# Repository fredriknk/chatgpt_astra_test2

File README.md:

# Codex EE-design test, human foreword
So, background, i saw the Chatgpt Astra demo for kicad design and wanted to try it out myself, i just have an Open AI plus subscription, so i had to use the LOW setting to not nuke my usage immidiatly. But it managed to make this design within my three usage resets. Im pretty damn impressed with the result, its not perfect, but it is a fully routed design with no drc errors made in under 3 hours with a 20$ subscription. I would say the most lacking part is the schematic, it is not very human readable, but i do understand why it is made as it is as ive tried multiple MCP's for ee design and wires in schematics becomes a hot mess with more than a few components. But now im out of resets so i thought i stop here. 

Initial repo: [my kicad template](https://github.com/fredriknk/kicad_template)
Initial promt: [prompt](https://github.com/fredriknk/chatgpt_astra_test2/blob/main/Prompt.md)

After the initial prompt i basically just said "Sounds like a good idea" to any questions

# ESP32 24 V current-loop interface - Rev A

A 100 x 80 mm, four-layer prototype with an ESP32-S3, one protected 4-20 mA input, and one sourcing 4-20 mA output. Power and signal grounds are shared; this is not an isolated interface.

The layout is fully routed. Final KiCad 9 checks report **zero ERC violations, zero DRC violations, zero unconnected items, and zero schematic/PCB parity errors**. The independent connectivity check covers 93 components and 273 connected pins. Hardware accuracy, fault survival, thermal performance, EMC and USB interoperability still require prototype testing.

| Start here | Contents |
|---|---|
| [Design and bring-up guide](DOCUMENTATION/DESIGN.md) | Wiring, protection, firmware interface, calibration and bench tests |
| [Fabrication notes](DOCUMENTATION/FABRICATION.md) | Stackup, USB impedance, assembly and procurement |
| [KiCad project](CAD/chatgpt_astra_test2/chatgpt_astra_test2.kicad_pro) | Editable schematic and PCB, with local libraries |
| [Schematic PDF](DOCUMENTATION/chatgpt_astra_test2_schematic.pdf) | Five schematic sheets |
| [Board layers PDF](DOCUMENTATION/chatgpt_astra_test2_board_prints.pdf) | Copper, mask, silkscreen and assembly views |
| [Layout verification](DOCUMENTATION/board_review/README.md) | Checks, USB length audit and milestones |
| [Manufacturing outputs](PRODUCTION/20260907_1303_chatgpt_astra_test2/) | Four copper layers, masks, silk, paste, outline, drills, BOM and placement CSV |
| [CI build log](DOCUMENTATION/ci_build.log) | Successful complete output-pipeline run |

## Regenerate and check

On Windows with KiCad 9 installed, run `generate_outputs.bat`. The equivalent command is:

```text
python build_outputs.py --project CAD/chatgpt_astra_test2/chatgpt_astra_test2.kicad_pro --iso --zip
```

The script fails on ERC/DRC violations and generates a new timestamped production folder. It does not place an order. `generate_outputs.sh` provides the same entry point on systems with KiCad on PATH. Set `KICAD9_3DMODEL_DIR` to the installed KiCad model library if needed.

The BOM is an engineering BOM: semiconductor part numbers are in Value fields, while several passives retain value/rating specifications rather than purchasing MPNs. Review procurement before ordering. Three installed 3D models are missing (USB connector, DAC and current driver); their footprints are present, but the STEP/render is not a complete mechanical assembly model.

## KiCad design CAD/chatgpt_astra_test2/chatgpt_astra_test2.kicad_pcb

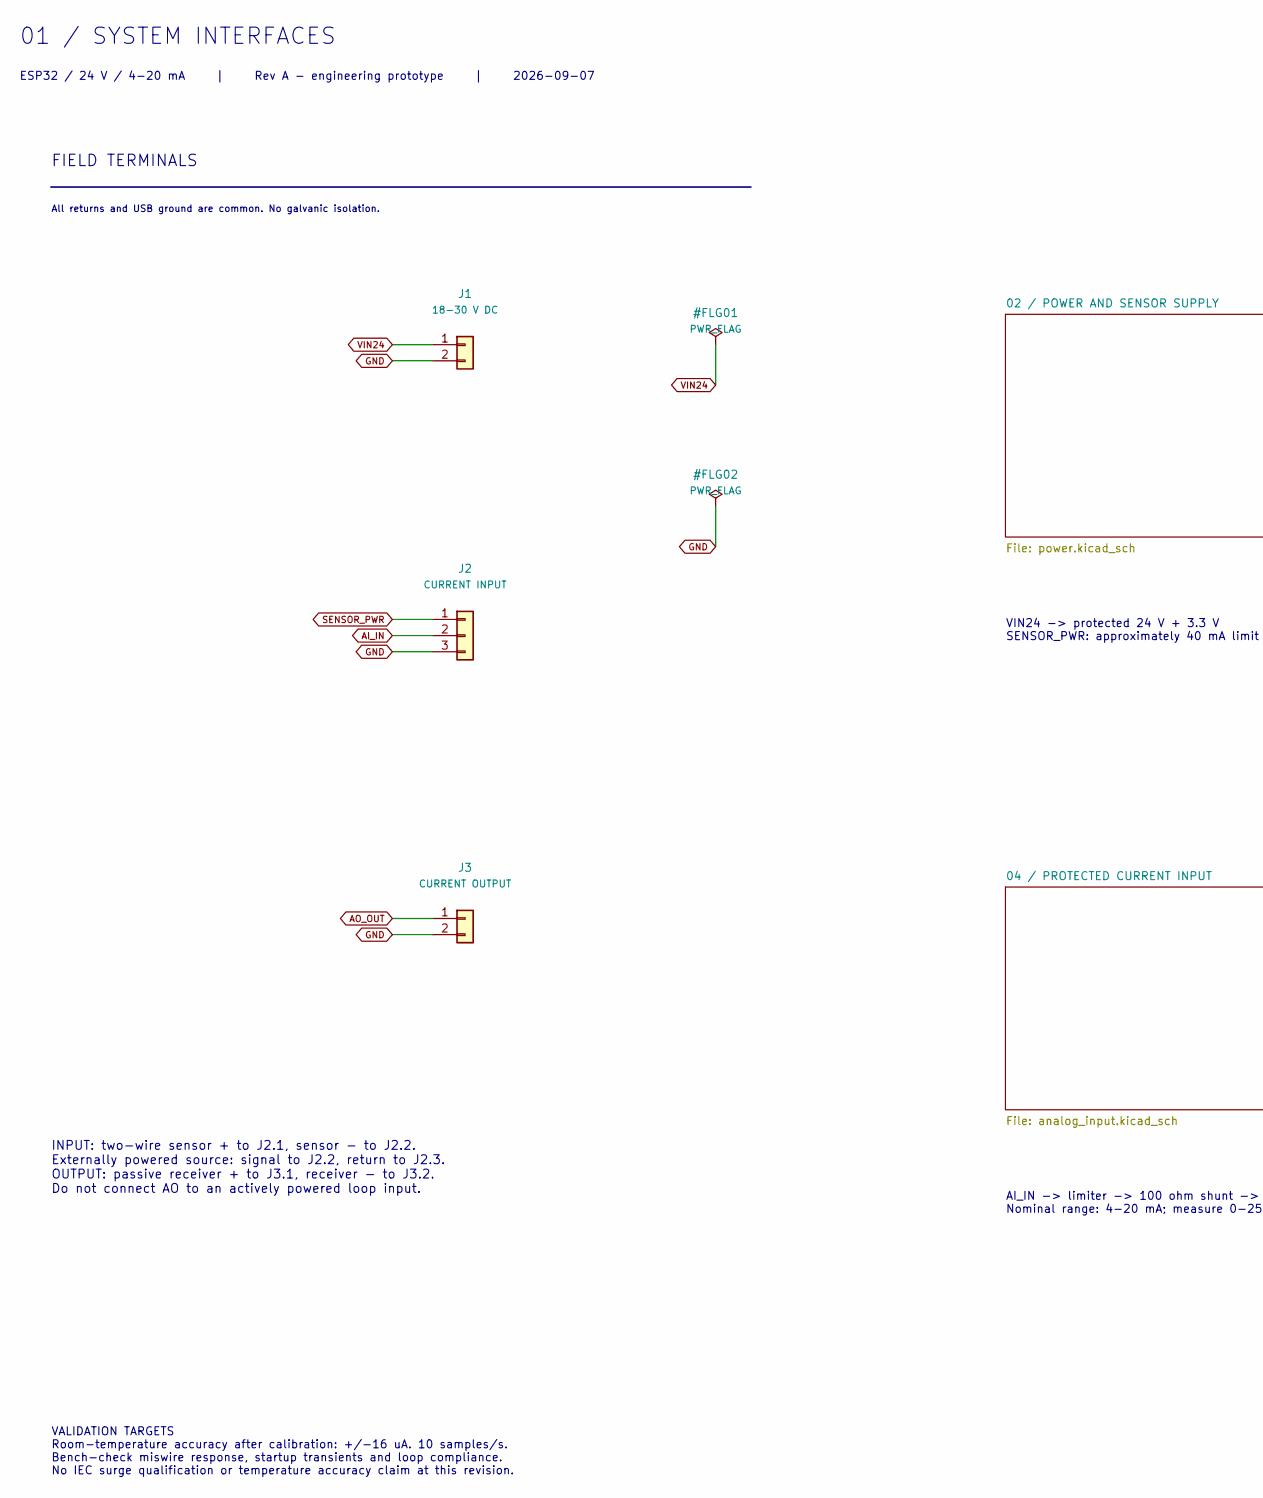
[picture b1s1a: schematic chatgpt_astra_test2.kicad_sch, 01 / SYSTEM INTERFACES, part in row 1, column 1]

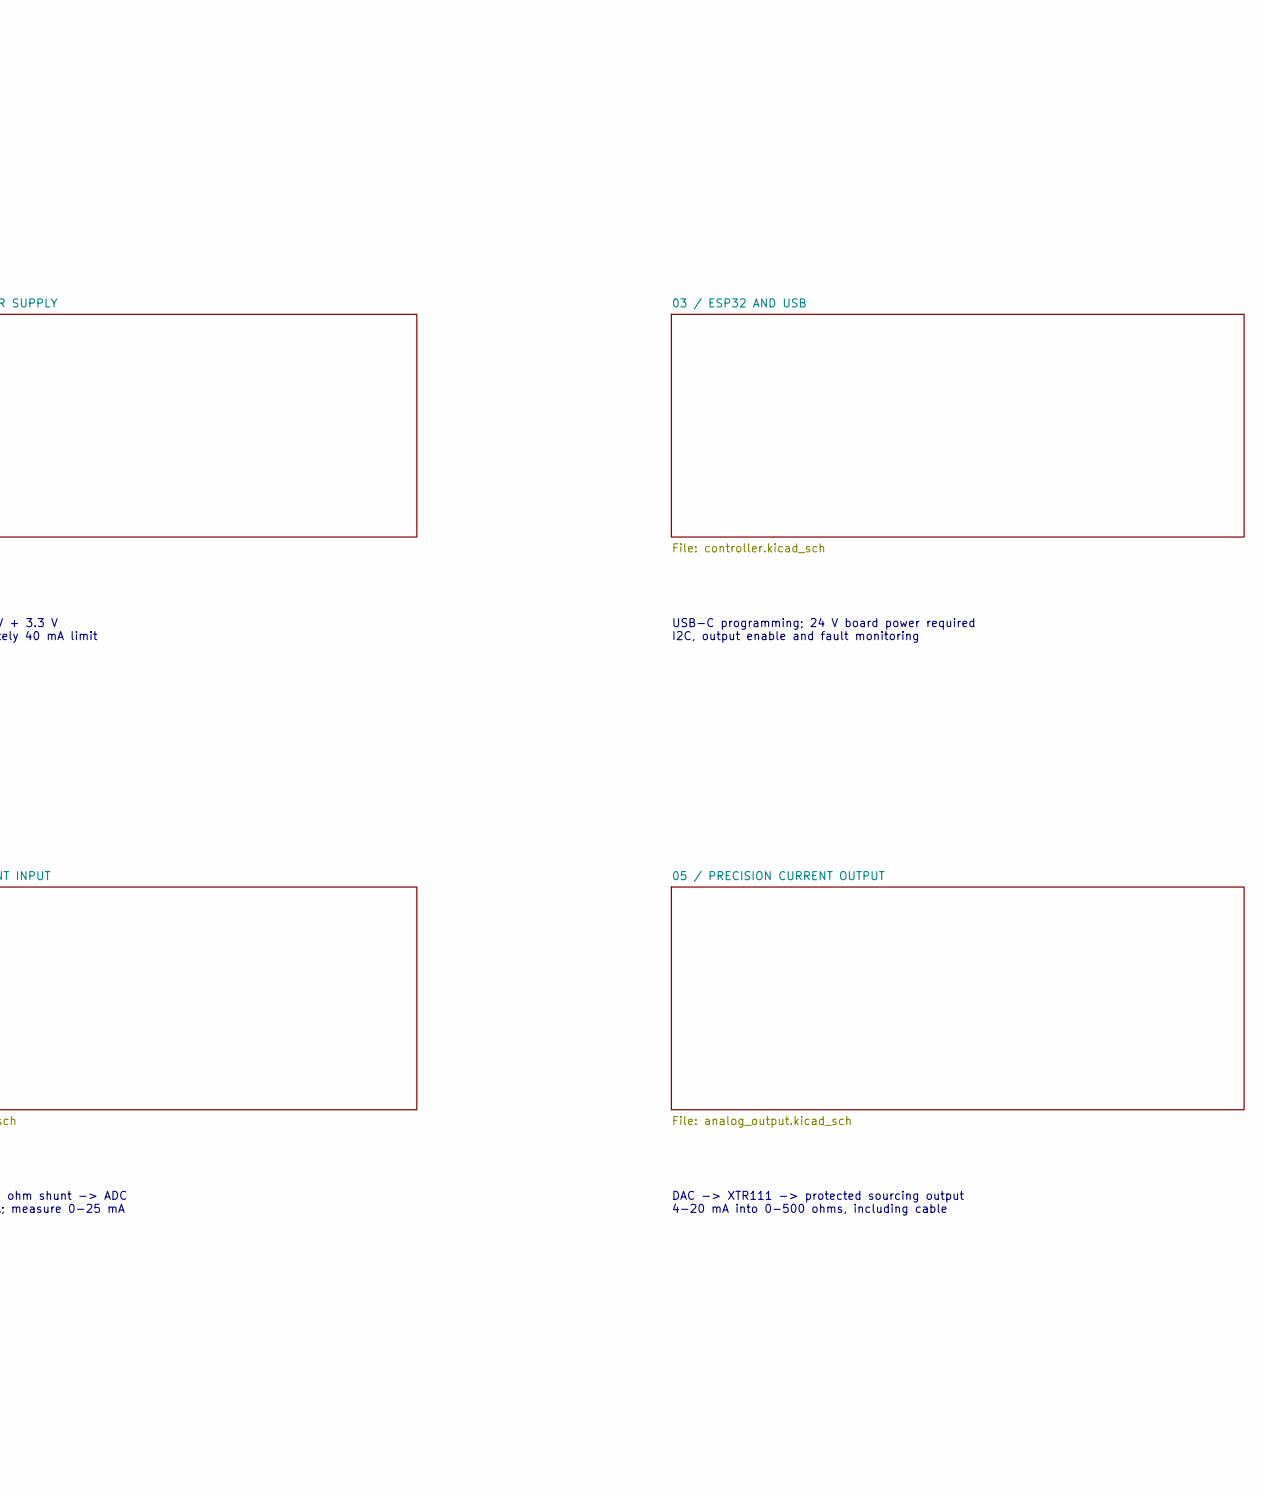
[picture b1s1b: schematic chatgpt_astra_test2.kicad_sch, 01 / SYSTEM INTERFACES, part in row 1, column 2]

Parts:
J1: 18-30 V DC; TerminalBlock_Phoenix_MKDS-1,5-2-5.08_1x02_P5.08mm_Horizont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
J2: CURRENT INPUT; TerminalBlock_Phoenix_MKDS-1,5-3-5.08_1x03_P5.08mm_Horizont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
J3: CURRENT OUTPUT; TerminalBlock_Phoenix_MKDS-1,5-2-5.08_1x02_P5.08mm_Horizont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

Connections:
AI_IN: J2.2; also elsewhere on the board
AO_OUT: J3.1; also elsewhere on the board
GND: J1.2, J2.3, J3.2; also elsewhere on the board
SENSOR_PWR: J2.1; also elsewhere on the board
VIN24: J1.1; also elsewhere on the board

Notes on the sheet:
01 / SYSTEM INTERFACES
ESP32 / 24 V / 4-20 mA | Rev A - engineering prototype | 2026-09-07
FIELD TERMINALS
All returns and USB ground are common. No galvanic isolation.
INPUT: two-wire sensor + to J2.1, sensor - to J2.2. Externally powered source: signal to J2.2, return to J2.3. OUTPUT: passive receiver + to J3.1, receiver - to J3.2. Do not connect AO to an actively powered loop input.
VIN24 -> protected 24 V + 3.3 V SENSOR_PWR: approximately 40 mA limit
USB-C programming; 24 V board power required I2C, output enable and fault monitoring
AI_IN -> limiter -> 100 ohm shunt -> ADC Nominal range: 4-20 mA; measure 0-25 mA
DAC -> XTR111 -> protected sourcing output 4-20 mA into 0-500 ohms, including cable
VALIDATION TARGETS Room-temperature accuracy after calibration: +/-16 uA. 10 samples/s. Bench-check miswire response, startup transients and loop compliance. No IEC surge qualification or temperature accuracy claim at this revision.

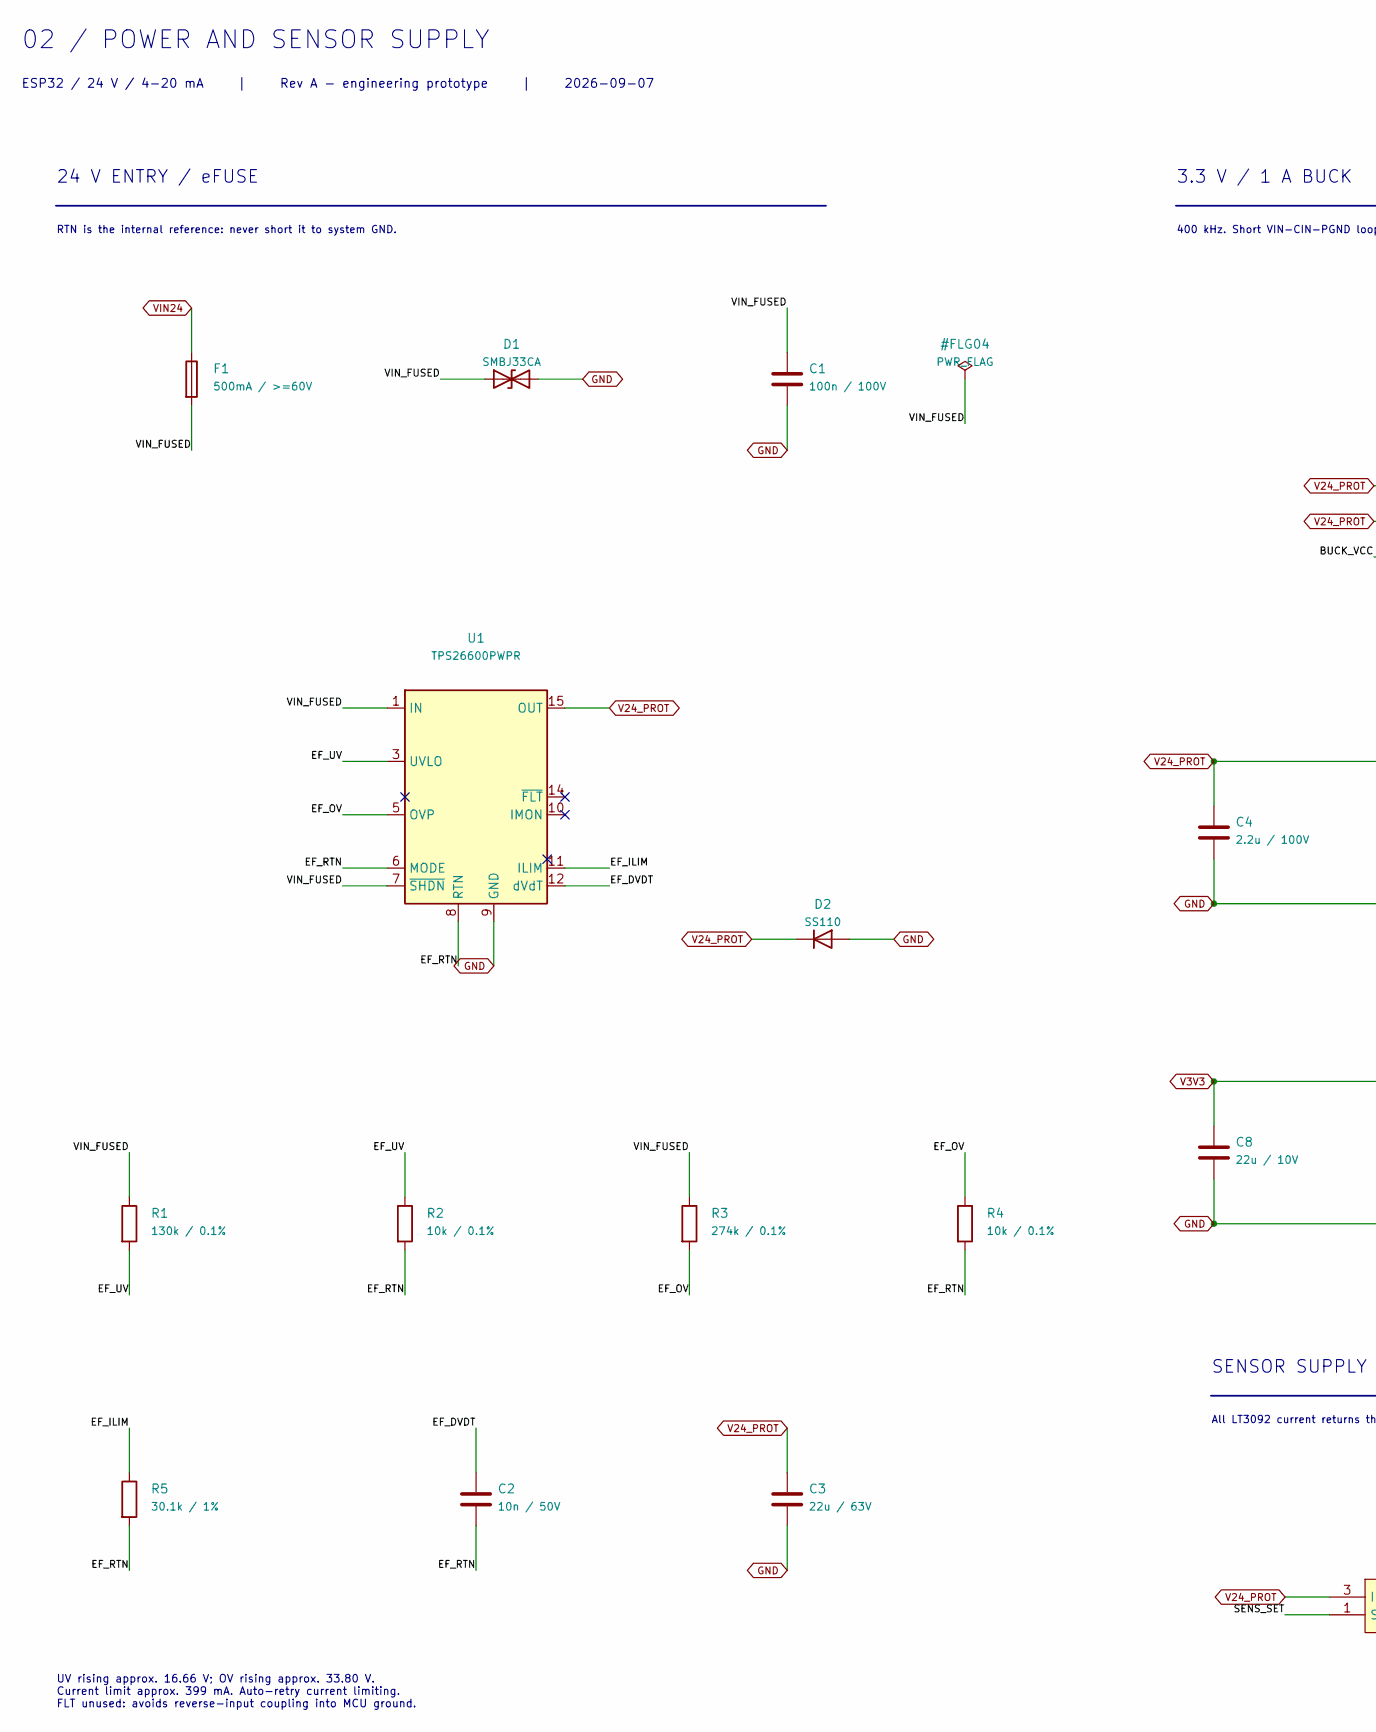
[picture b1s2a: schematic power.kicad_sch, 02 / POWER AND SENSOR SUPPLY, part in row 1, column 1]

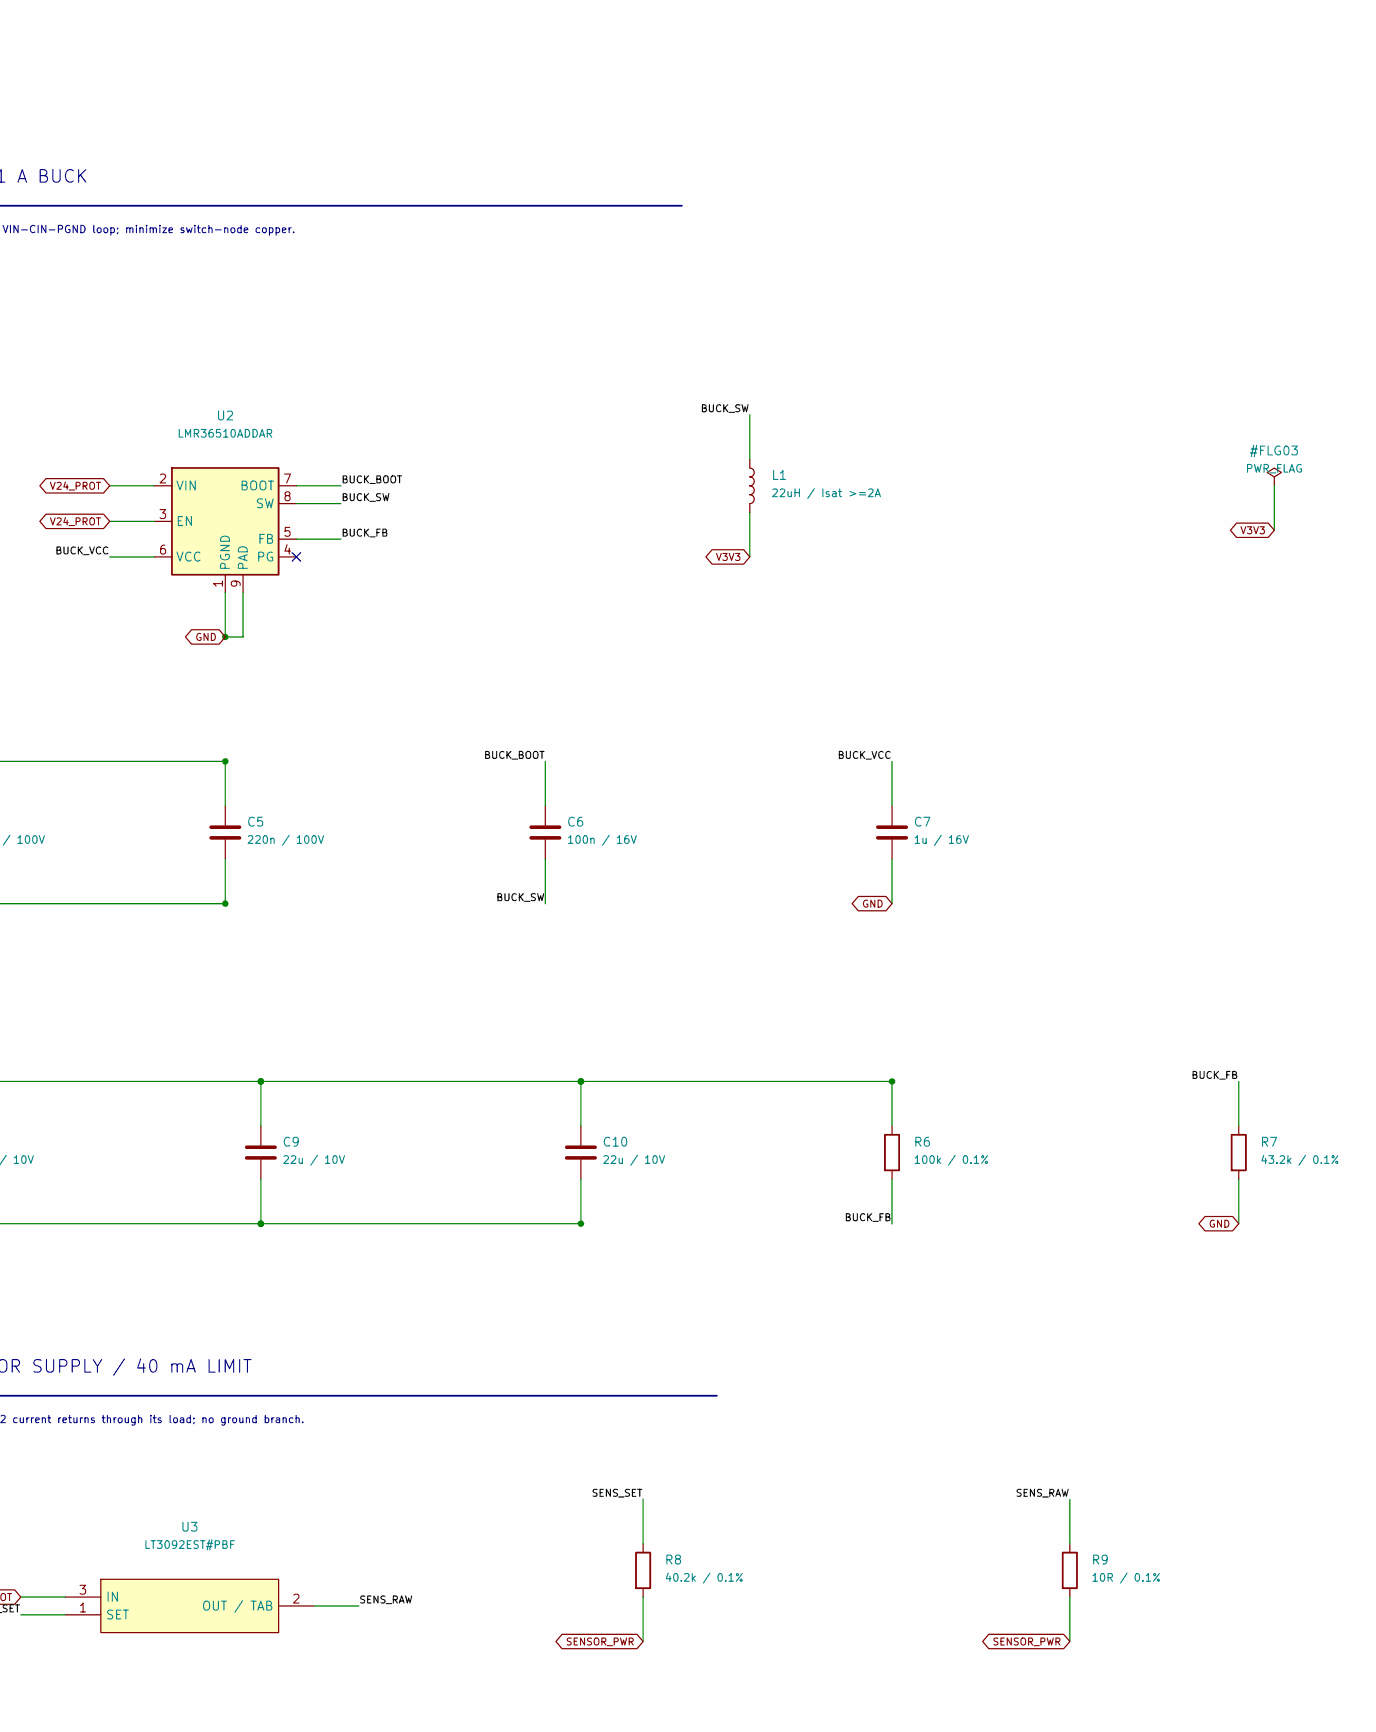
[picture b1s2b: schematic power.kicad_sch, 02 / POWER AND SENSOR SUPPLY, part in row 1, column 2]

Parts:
C1: 100n / 100V; C_0805_2012Metric
C2: 10n / 50V; C_0805_2012Metric
C3: 22u / 63V; C_1210_3225Metric
C4: 2.2u / 100V; C_1210_3225Metric
C5: 220n / 100V; C_0805_2012Metric
C6: 100n / 16V; C_0805_2012Metric
C7: 1u / 16V; C_0805_2012Metric
C8, C9, C10: 22u / 10V; C_1206_3216Metric
D1: SMBJ33CA; D_SMB
D2: SS110; D_SMA
F1: 500mA / >=60V; Fuse_1206_3216Metric
L1: 22uH / Isat >=2A; L_Bourns_SRN6045TA
R1: 130k / 0.1%; R_0805_2012Metric
R2, R4: 10k / 0.1%; R_0805_2012Metric
R3: 274k / 0.1%; R_0805_2012Metric
R5: 30.1k / 1%; R_0805_2012Metric
R6: 100k / 0.1%; R_0805_2012Metric
R7: 43.2k / 0.1%; R_0805_2012Metric
R8: 40.2k / 0.1%; R_0805_2012Metric
R9: 10R / 0.1%; R_0805_2012Metric
U1: TPS26600PWPR; HTSSOP-16-1EP_4.4x5mm_P0.65mm_EP3.4x5mm_Mask2.66x2.46mm_The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
U2: LMR36510ADDAR; Texas_HTSOP-8-1EP_3.9x4.9mm_P1.27mm_EP2.95x4.9mm_Mask2.4x3.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
U3: LT3092EST#PBF; SOT-223-3_TabPin2

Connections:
/02 / POWER AND SENSOR SUPPLY/BUCK_BOOT: C6.1, U2.7 (BOOT)
/02 / POWER AND SENSOR SUPPLY/BUCK_FB: R6.2, R7.1, U2.5 (FB)
/02 / POWER AND SENSOR SUPPLY/BUCK_SW: C6.2, L1.1, U2.8 (SW)
/02 / POWER AND SENSOR SUPPLY/BUCK_VCC: C7.1, U2.6 (VCC)
/02 / POWER AND SENSOR SUPPLY/EF_DVDT: C2.1, U1.12 (dVdT)
/02 / POWER AND SENSOR SUPPLY/EF_ILIM: R5.1, U1.11 (ILIM)
/02 / POWER AND SENSOR SUPPLY/EF_OV: R3.2, R4.1, U1.5 (OVP)
/02 / POWER AND SENSOR SUPPLY/EF_RTN: C2.2, R2.2, R4.2, R5.2, U1.6 (MODE), U1.8 (RTN), U1.17 (RTN)
/02 / POWER AND SENSOR SUPPLY/EF_UV: R1.2, R2.1, U1.3 (UVLO)
/02 / POWER AND SENSOR SUPPLY/SENS_RAW: R9.1, U3.2 (OUT / TAB)
/02 / POWER AND SENSOR SUPPLY/SENS_SET: R8.1, U3.1 (SET)
/02 / POWER AND SENSOR SUPPLY/VIN_FUSED: C1.1, D1.1 (A1), F1.2, R1.1, R3.1, U1.1 (IN), U1.2 (IN), U1.7 (~SHDN)
GND: C1.2, C3.2, C4.2, C5.2, C7.2, C8.2, C9.2, C10.2, D1.2 (A2), D2.2 (A), R7.2, U1.9 (GND), U2.1 (PGND), U2.9 (PAD); also elsewhere on the board
SENSOR_PWR: R8.2, R9.2; also elsewhere on the board
V3V3: C8.1, C9.1, C10.1, L1.2, R6.1; also elsewhere on the board
V24_PROT: C3.1, C4.1, C5.1, D2.1 (K), U1.15 (OUT), U1.16 (OUT), U2.2 (VIN), U2.3 (EN), U3.3 (IN); also elsewhere on the board
VIN24: F1.1; also elsewhere on the board

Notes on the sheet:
02 / POWER AND SENSOR SUPPLY
ESP32 / 24 V / 4-20 mA | Rev A - engineering prototype | 2026-09-07
24 V ENTRY / eFUSE
RTN is the internal reference: never short it to system GND.
UV rising approx. 16.66 V; OV rising approx. 33.80 V. Current limit approx. 399 mA. Auto-retry current limiting. FLT unused: avoids reverse-input coupling into MCU ground.
3.3 V / 1 A BUCK
400 kHz. Short VIN-CIN-PGND loop; minimize switch-node copper.
SENSOR SUPPLY / 40 mA LIMIT
All LT3092 current returns through its load; no ground branch.

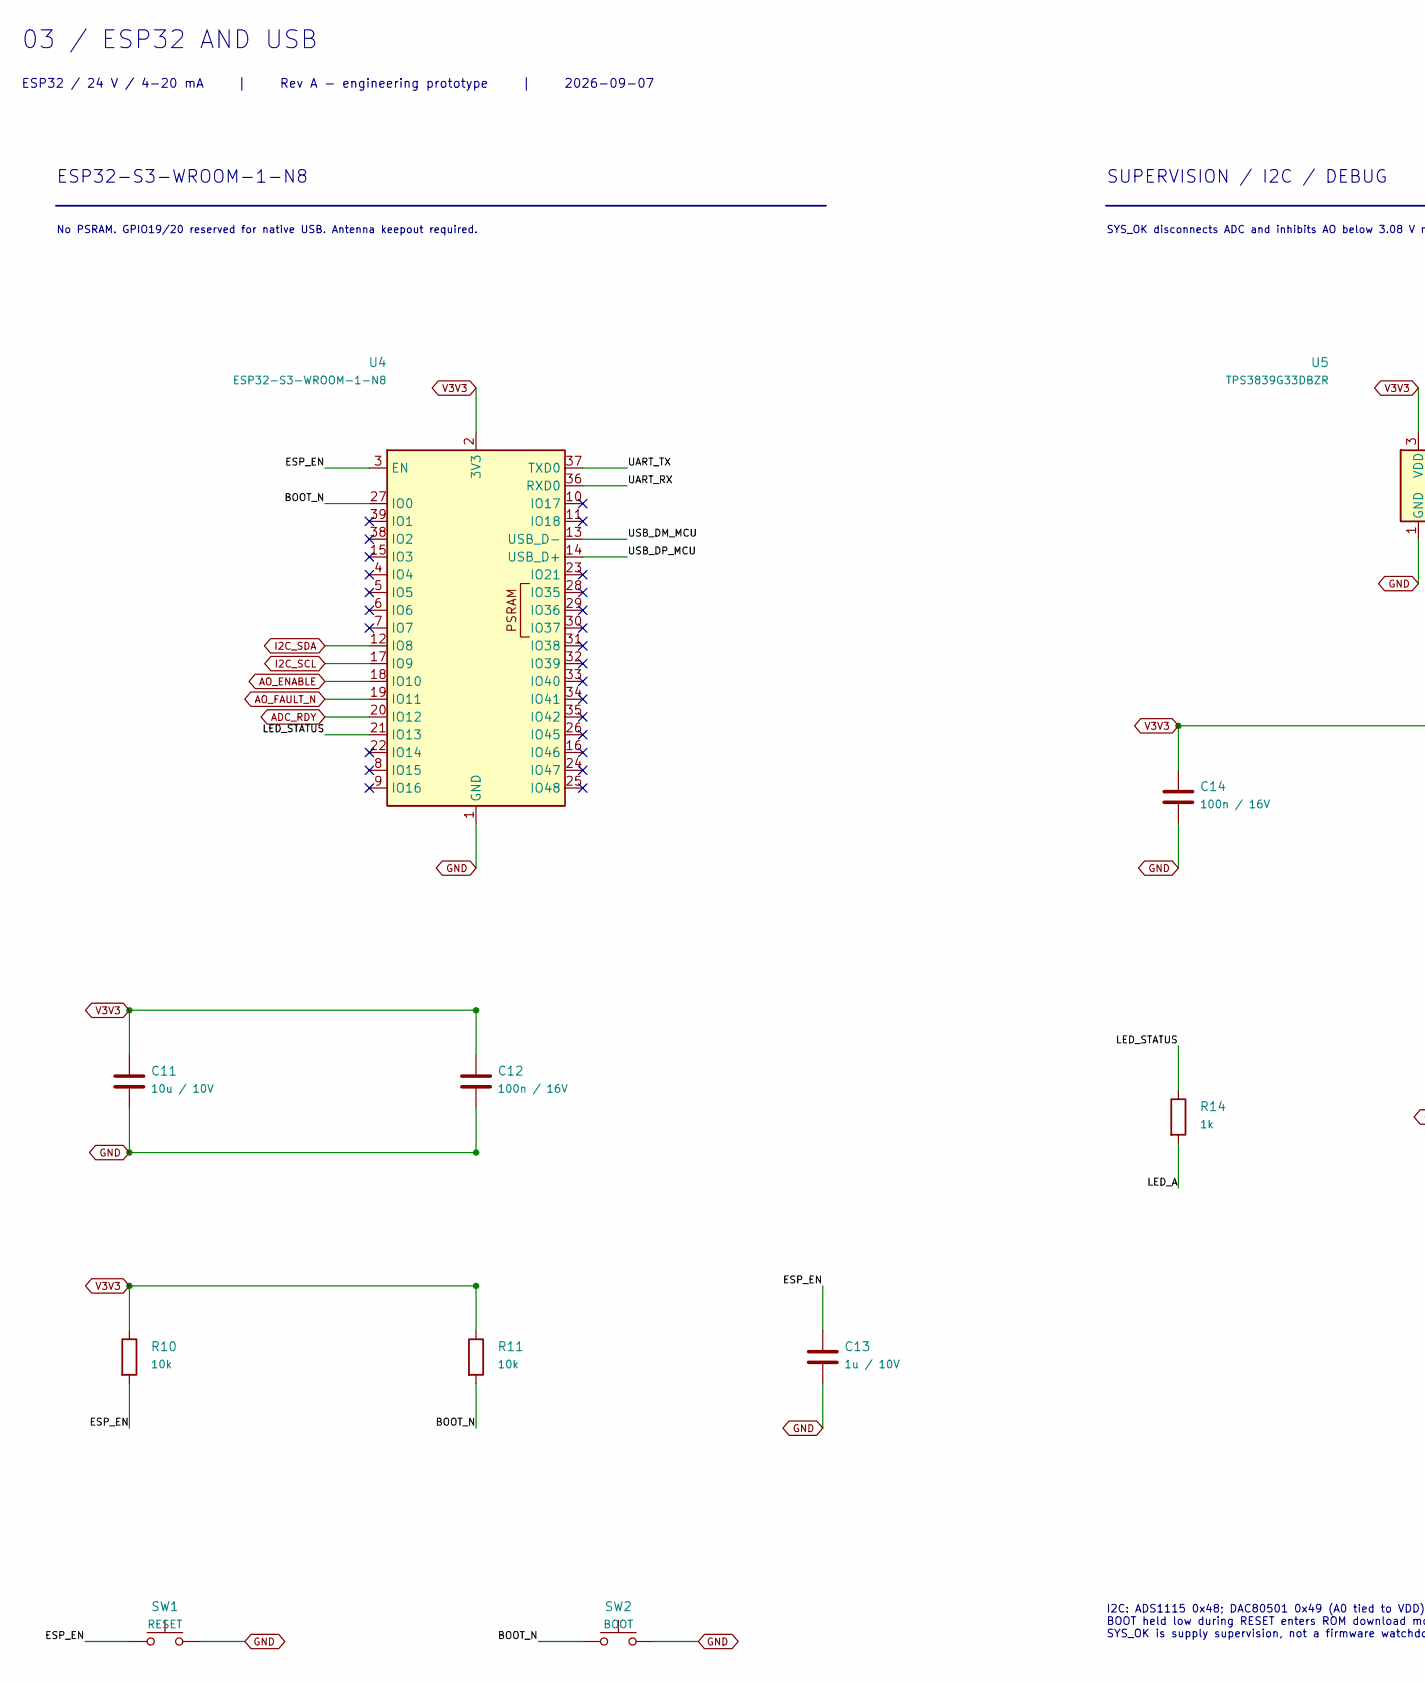
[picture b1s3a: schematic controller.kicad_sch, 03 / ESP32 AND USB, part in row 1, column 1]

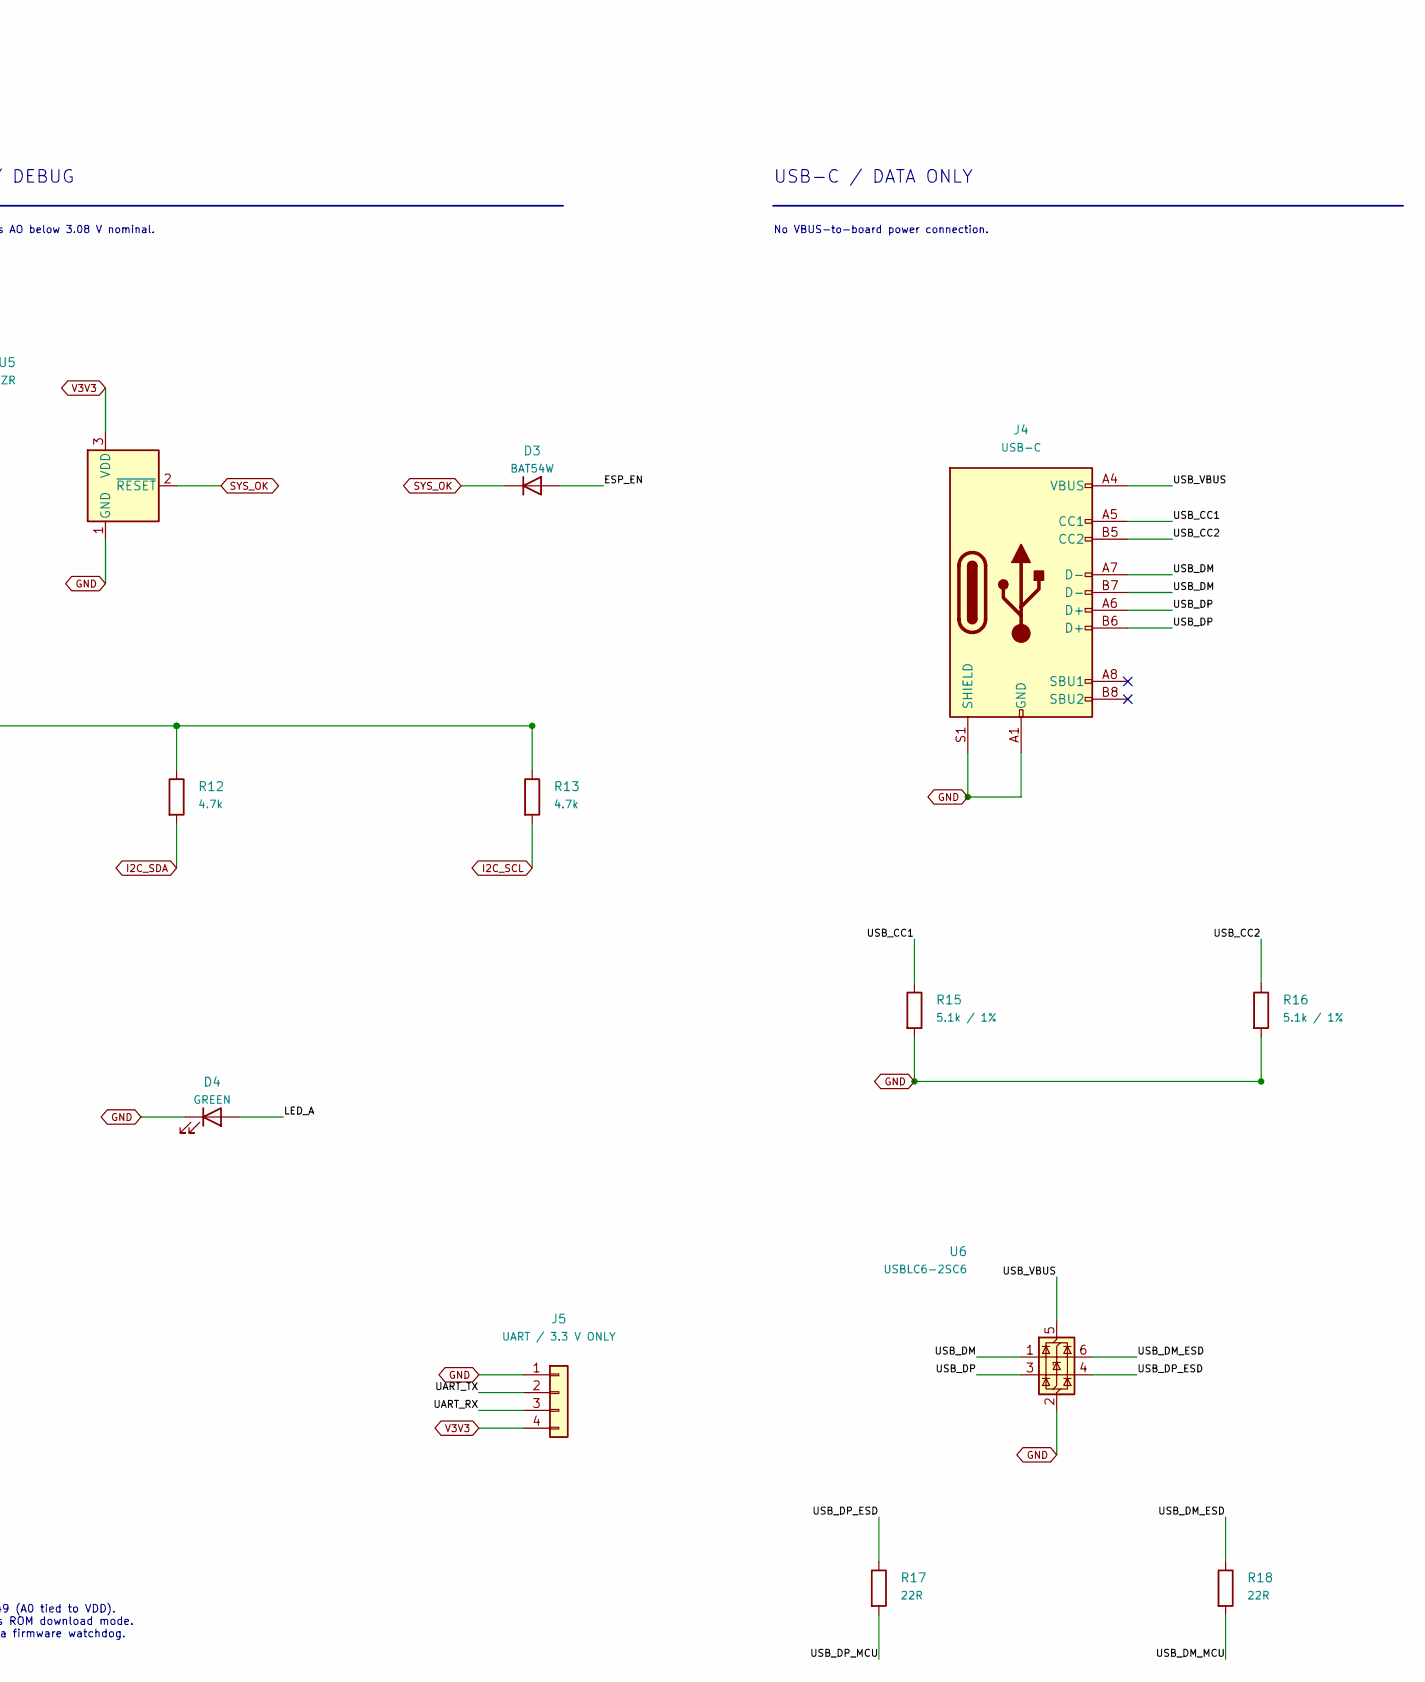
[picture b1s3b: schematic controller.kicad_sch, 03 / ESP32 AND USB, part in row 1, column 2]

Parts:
C11: 10u / 10V; C_0805_2012Metric
C12, C14: 100n / 16V; C_0805_2012Metric
C13: 1u / 10V; C_0805_2012Metric
D3: BAT54W; D_SOD-123
D4: GREEN; LED_0805_2012Metric
J4: USB-C; USB_C_Receptacle_HRO_TYPE-C-31-M-12
J5: UART / 3.3 V ONLY; PinHeader_1x04_P2.54mm_Vertical
R10, R11: 10k; R_0805_2012Metric
R12, R13: 4.7k; R_0805_2012Metric
R14: 1k; R_0805_2012Metric
R15, R16: 5.1k / 1%; R_0805_2012Metric
R17, R18: 22R; R_0805_2012Metric
SW1: RESET; SW_SPST_TL3342
SW2: BOOT; SW_SPST_TL3342
U4: ESP32-S3-WROOM-1-N8; ESP32-S3-WROOM-1
U5: TPS3839G33DBZR; SOT-23
U6: USBLC6-2SC6; SOT-23-6

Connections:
/03 / ESP32 AND USB/BOOT_N: R11.2, SW2.1, U4.27 (IO0)
/03 / ESP32 AND USB/ESP_EN: C13.1, D3.2 (A), R10.2, SW1.1, U4.3 (EN)
/03 / ESP32 AND USB/LED_A: D4.2 (A), R14.2
/03 / ESP32 AND USB/LED_STATUS: R14.1, U4.21 (IO13)
/03 / ESP32 AND USB/UART_RX: J5.3, U4.36 (RXD0)
/03 / ESP32 AND USB/UART_TX: J5.2, U4.37 (TXD0)
/03 / ESP32 AND USB/USB_CC1: J4.A5 (CC1), R15.1
/03 / ESP32 AND USB/USB_CC2: J4.B5 (CC2), R16.1
/03 / ESP32 AND USB/USB_DM: J4.A7 (D-), J4.B7 (D-), U6.1 (I/O1)
/03 / ESP32 AND USB/USB_DM_ESD: R18.1, U6.6 (I/O1)
/03 / ESP32 AND USB/USB_DM_MCU: R18.2, U4.13 (USB_D-)
/03 / ESP32 AND USB/USB_DP: J4.A6 (D+), J4.B6 (D+), U6.3 (I/O2)
/03 / ESP32 AND USB/USB_DP_ESD: R17.1, U6.4 (I/O2)
/03 / ESP32 AND USB/USB_DP_MCU: R17.2, U4.14 (USB_D+)
/03 / ESP32 AND USB/USB_VBUS: J4.A4 (VBUS), J4.A9 (VBUS), J4.B4 (VBUS), J4.B9 (VBUS), U6.5 (VBUS)
ADC_RDY: U4.20 (IO12); also elsewhere on the board
AO_ENABLE: U4.18 (IO10); also elsewhere on the board
AO_FAULT_N: U4.19 (IO11); also elsewhere on the board
GND: C11.2, C12.2, C13.2, C14.2, D4.1 (K), J4.A1 (GND), J4.A12 (GND), J4.B1 (GND), J4.B12 (GND), J4.S1 (SHIELD), J5.1, R15.2, R16.2, SW1.2, SW2.2, U4.1 (GND), U4.40 (GND), U4.41 (GND), U5.1 (GND), U6.2 (GND); also elsewhere on the board
I2C_SCL: R13.2, U4.17 (IO9); also elsewhere on the board
I2C_SDA: R12.2, U4.12 (IO8); also elsewhere on the board
SYS_OK: D3.1 (K), U5.2 (~RESET); also elsewhere on the board
V3V3: C11.1, C12.1, C14.1, J5.4, R10.1, R11.1, R12.1, R13.1, U4.2 (3V3), U5.3 (VDD); also elsewhere on the board

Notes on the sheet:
03 / ESP32 AND USB
ESP32 / 24 V / 4-20 mA | Rev A - engineering prototype | 2026-09-07
ESP32-S3-WROOM-1-N8
No PSRAM. GPIO19/20 reserved for native USB. Antenna keepout required.
SUPERVISION / I2C / DEBUG
SYS_OK disconnects ADC and inhibits AO below 3.08 V nominal.
I2C: ADS1115 0x48; DAC80501 0x49 (A0 tied to VDD). BOOT held low during RESET enters ROM download mode. SYS_OK is supply supervision, not a firmware watchdog.
USB-C / DATA ONLY
No VBUS-to-board power connection.
